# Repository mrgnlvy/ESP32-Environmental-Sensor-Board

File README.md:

# ESP32-Environmental-Sensor-Board

4-layer ESP32-C3 IoT PCB with USB-C charging and data transfer, along with environmental sensors, a battery charge manger,  an OLED display, and SD storage for remote data logging capabilities.

### Features

- **Microcontroller**: ESP32-C3-02 for Wi-Fi/BLE
- **Power Inputs**:
  - USB-C connector for charging and data transfer.
  - LiPo battery connector with onboard charging circuitry.
- **Sensors and Modules**:
  - BME280 for temperature, humidity, and pressure sensing.
  - Ambient light and sound sensors.
  - Mini SD card reader for data storage.
  - Flash memory for additional storage.
- **Power Management**: TP4056 IC for single-cell Li-ion battery charging with thermal regulation.
- **Battery Protection**: Integrated under-voltage lockout and trickle charging.
- **Display**: I2C OLED for real-time data visualization.
- **Indicators**: LED indicators for charge status (charging and full).

### Design

4-layer design:
- **Top**: Signals
- **Inner 1**: Ground Plane
- **Inner 2**: Power Plane
- **Bottom**: Signals

### Applications

- IoT edge devices for environmental monitoring.
- Battery-powered data logging systems.
- Prototyping platform for ESP32-based projects.

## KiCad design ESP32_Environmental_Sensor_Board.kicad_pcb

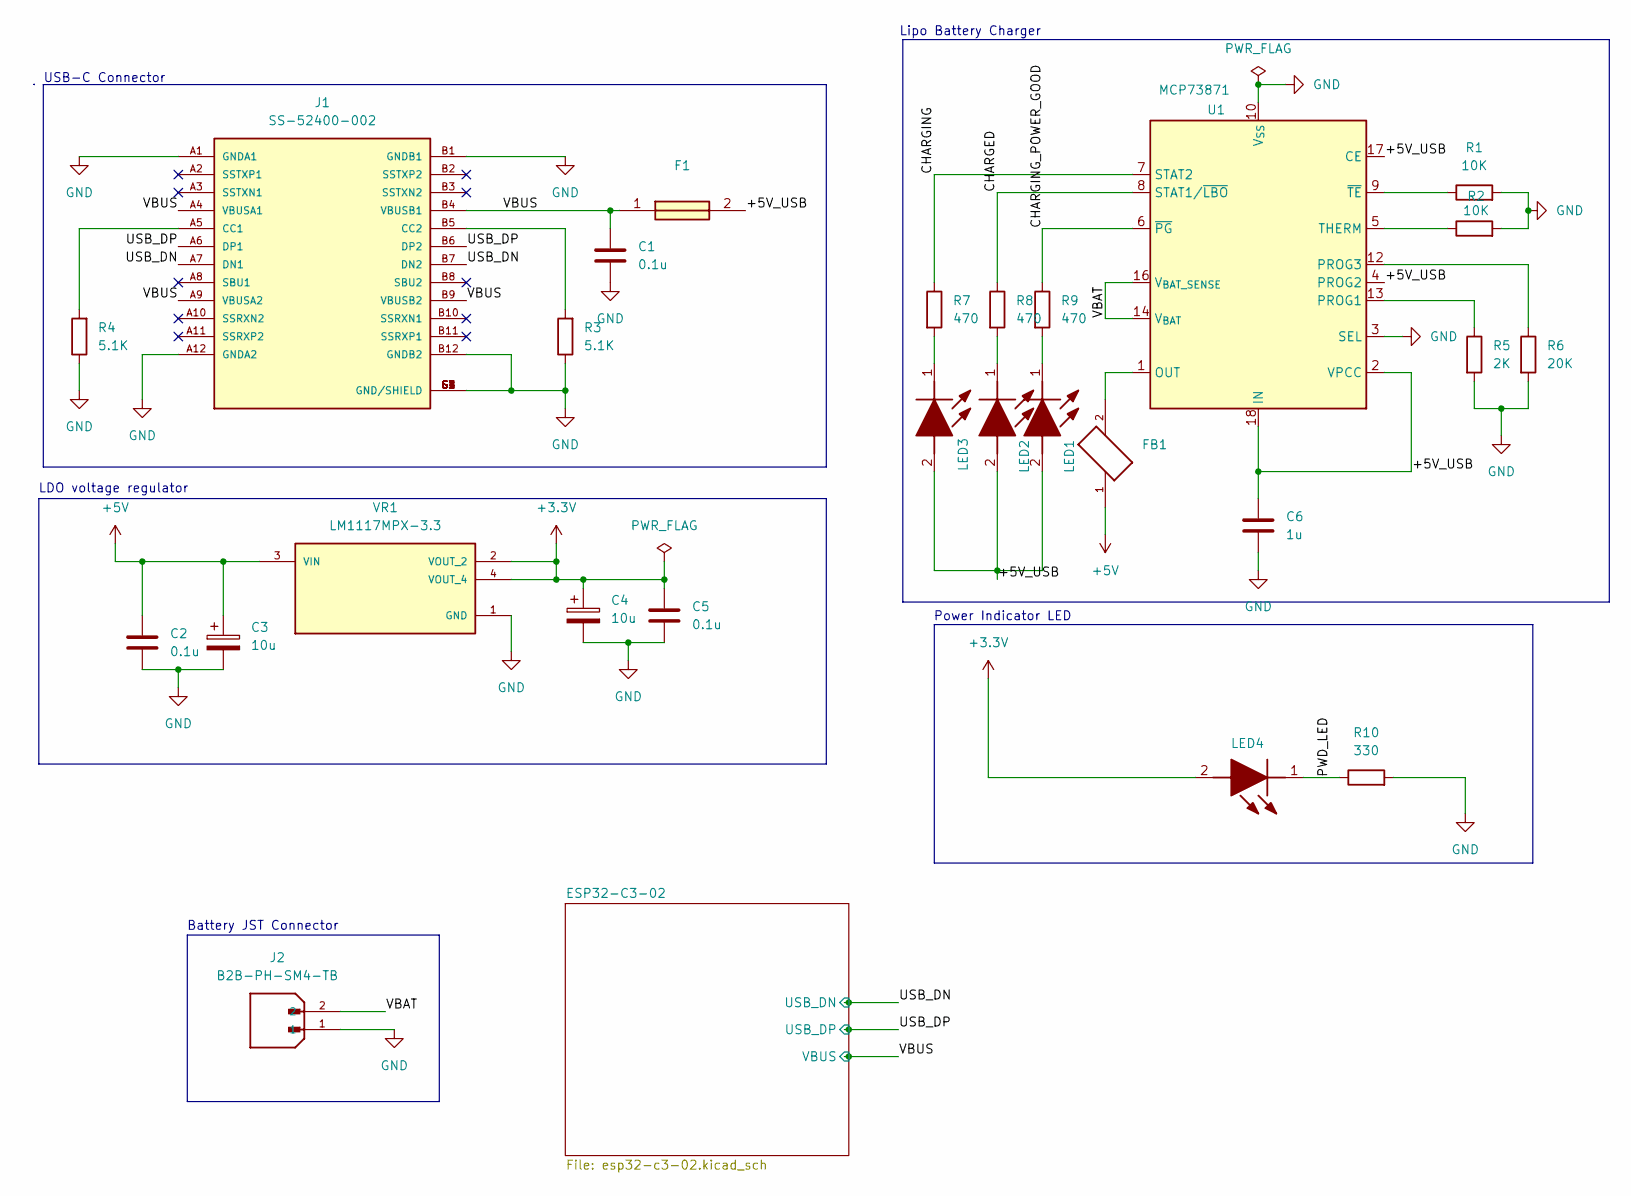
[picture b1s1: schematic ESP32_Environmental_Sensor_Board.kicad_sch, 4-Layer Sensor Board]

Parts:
C1, C2, C5: 0.1u; C_0805_2012Metric
C3, C4: 10u; T491A
C6: 1u; C_0805_2012Metric
F1: 0ZCH0110AF2E; FUSC3226X100N; Manufacturer_Part_Number 0ZCH0110AF2E
FB1: FBMJ2125HM330-T; BEADC2012X105N
J1: SS-52400-002; BELFUSE_SS-52400-002; PARTREV A0
J2: B2B-PH-SM4-TB; JST_B2B-PH-SM4-TB; PARTREV N/A
LED1: LTST-C170TBKT; LEDC2012X120N; Manufacturer_Part_Number LTST-C170TBKT; Mouser Part Number 859-LTST-C170TBKT
LED2: LTST-C170GKT; LEDC2012X120N; Manufacturer_Part_Number LTST-C170GKT; Mouser Part Number 859-LTST-C170GKT
LED3, LED4: LTST-C170KRKT; LEDC2012X120N; Manufacturer_Part_Number LTST-C170KRKT; Mouser Part Number 859-LTST-C170KRKT
R1, R2: 10K; R_0805_2012Metric
R3, R4: 5.1K; R_0805_2012Metric
R5: 2K; R_0805_2012Metric
R6: 20K; R_0805_2012Metric
R7, R8, R9: 470; R_0805_2012Metric
R10: 330; R_0805_2012Metric
U1: MCP73871; QFN-20-1EP_4x4mm_P0.5mm_EP2.5x2.5mm
VR1: LM1117MPX-3.3; VREG_LM1117MPX-3.3

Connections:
+3.3V: C4.1, C5.1, LED4.2 (A), VR1.2 (VOUT_2), VR1.4 (VOUT_4); also elsewhere on the board
+5V: C2.1, C3.1, FB1.1, VR1.3 (VIN)
/+5V_USB: C6.1, F1.2, LED1.2 (A), LED2.2 (A), LED3.2 (A), U1.2 (VPCC), U1.4 (PROG2), U1.17 (CE), U1.18 (IN), U1.19 (IN)
/CHARGED: R8.1, U1.8 (STAT1/~LBO)
/CHARGING: R7.1, U1.7 (STAT2)
/CHARGING_POWER_GOOD: R9.1, U1.6 (~PG)
/PWD_LED: LED4.1 (K), R10.1
/USB_DN: J1.A7 (DN1), J1.B7 (DN2); also elsewhere on the board
/USB_DP: J1.A6 (DP1), J1.B6 (DP2); also elsewhere on the board
/VBAT: J2.2, U1.14 (V_{BAT}), U1.15 (V_{BAT}), U1.16 (V_{BAT_SENSE})
/VBUS: C1.1, F1.1, J1.A4 (VBUSA1), J1.A9 (VBUSA2), J1.B4 (VBUSB1), J1.B9 (VBUSB2); also elsewhere on the board
GND: C1.2, C2.2, C3.2, C4.2, C5.2, C6.2, J1.A1 (GNDA1), J1.A12 (GNDA2), J1.B1 (GNDB1), J1.B12 (GNDB2), J1.G1 (GND/SHIELD), J1.G2 (GND/SHIELD), J1.G3 (GND/SHIELD), J1.G4 (GND/SHIELD), J1.S1 (GND/SHIELD), J1.S2 (GND/SHIELD), J1.S3 (GND/SHIELD), J1.S4 (GND/SHIELD), J2.1, R1.2, R2.2, R3.1, R4.1, R5.2, R6.2, R10.2, U1.3 (SEL), U1.10 (V_{SS}), U1.11 (V_{SS}), U1.21 (V_{SS}), VR1.1 (GND); also elsewhere on the board
unnamed: FB1.2, U1.1 (OUT), U1.20 (OUT)
unnamed: J1.A5 (CC1), R4.2
unnamed: J1.B5 (CC2), R3.2
unnamed: LED1.1 (K), R9.2
unnamed: LED2.1 (K), R8.2
unnamed: LED3.1 (K), R7.2
unnamed: R5.1, U1.13 (PROG1)
unnamed: R6.1, U1.12 (PROG3)
unnamed: R2.1, U1.5 (THERM)
unnamed: R1.1, U1.9 (~TE)

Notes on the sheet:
Battery JST Connector
USB-C Connector
Lipo Battery Charger
Power Indicator LED
LDO voltage regulator

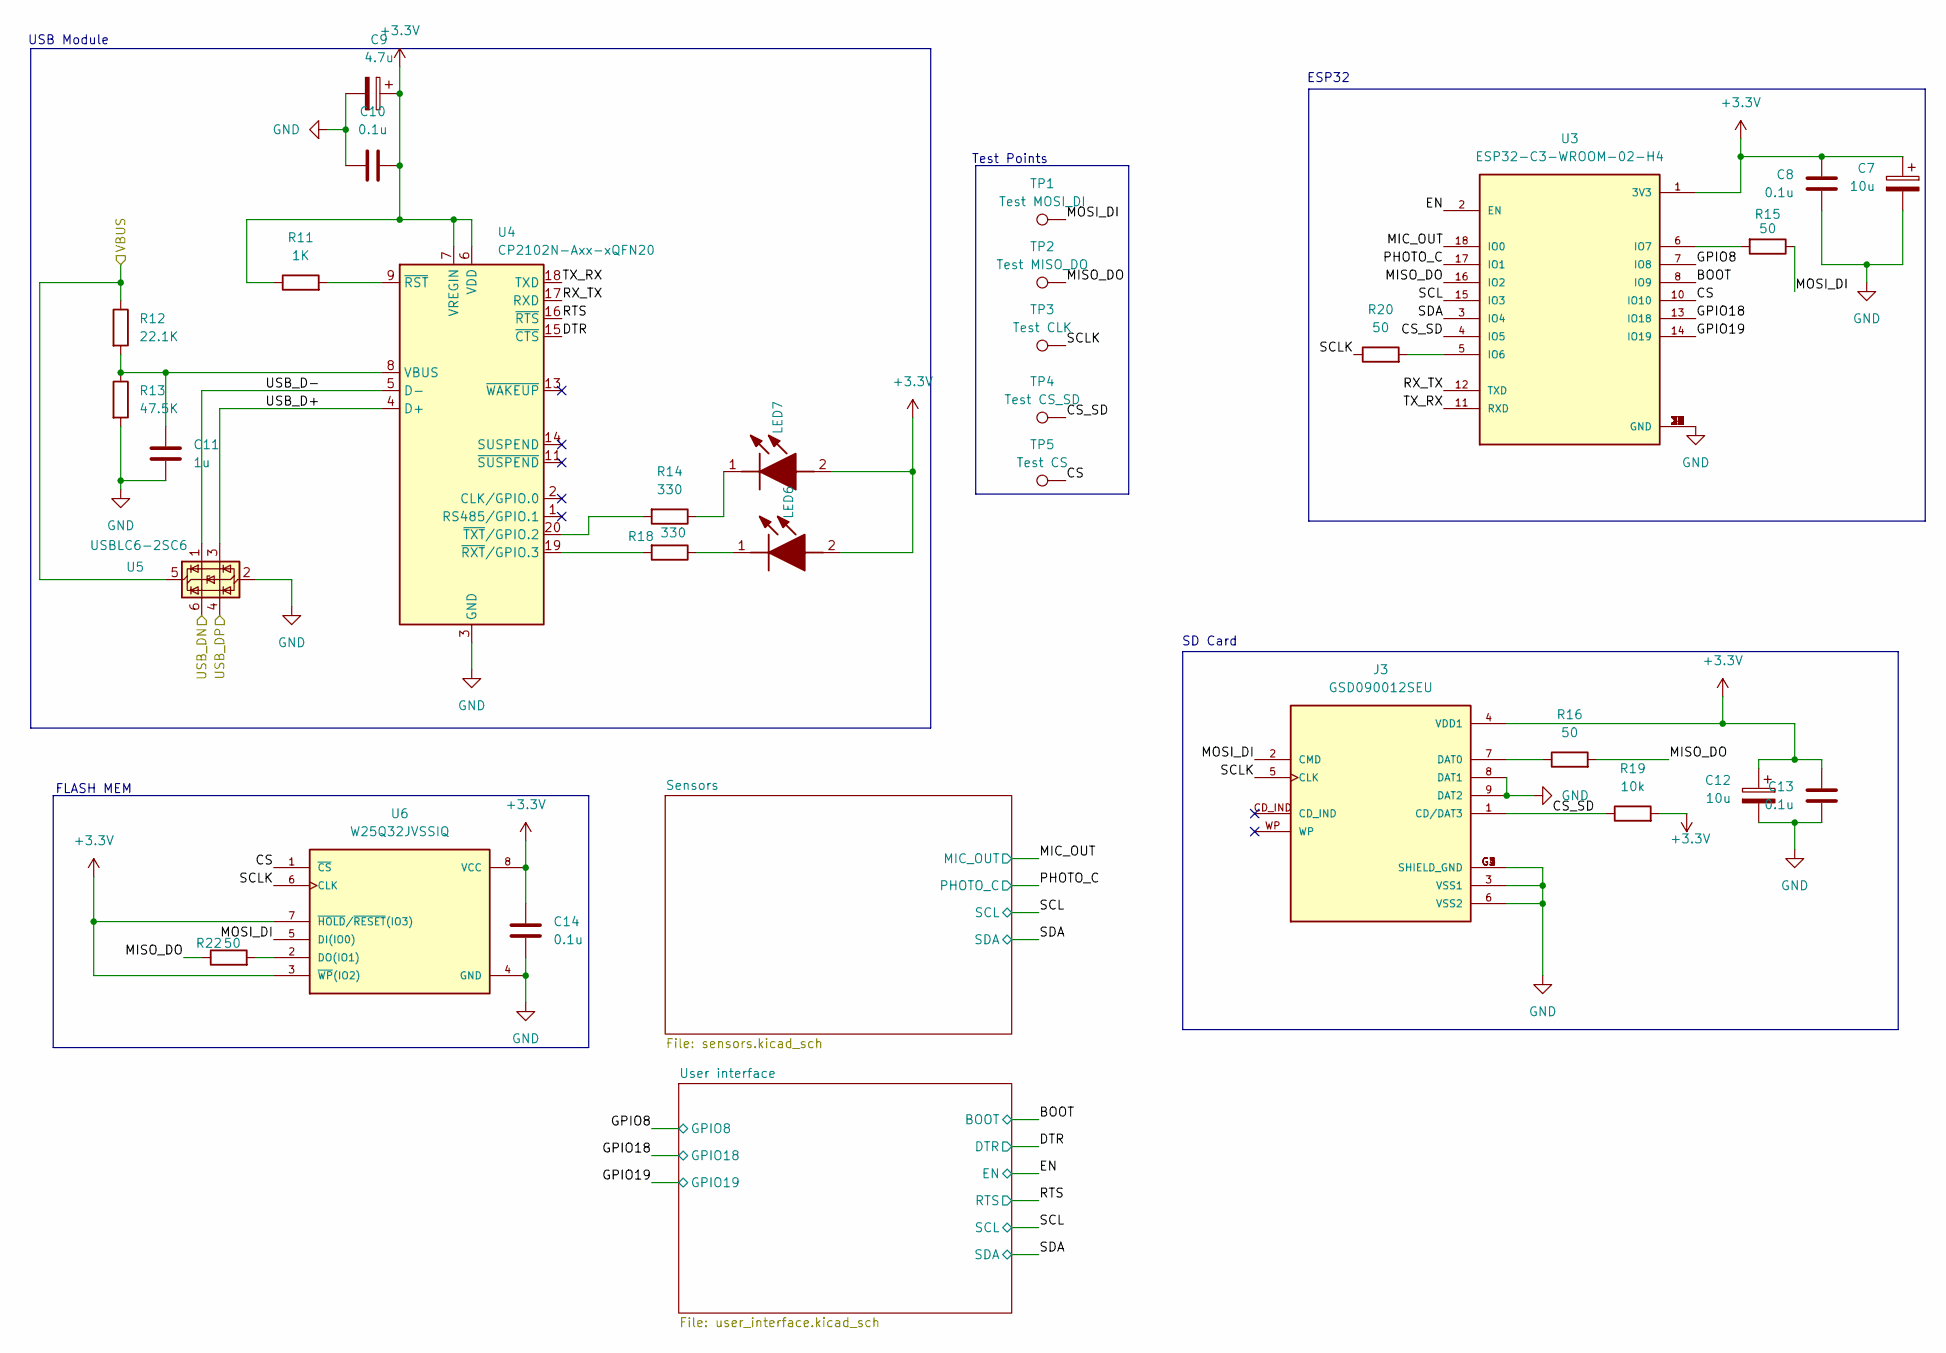
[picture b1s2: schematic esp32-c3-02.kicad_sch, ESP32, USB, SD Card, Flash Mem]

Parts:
C7, C12: 10u; T491A
C8, C10, C13, C14: 0.1u; C_0805_2012Metric
C9: 4.7u; T491A
C11: 1u; C_0805_2012Metric
J3: GSD090012SEU; AMPHENOL_GSD090012SEU; PARTREV E
LED6: LTST-C170TBKT; LEDC2012X120N; Manufacturer_Part_Number LTST-C170TBKT; Mouser Part Number 859-LTST-C170TBKT
LED7: LTST-C170GKT; LEDC2012X120N; Manufacturer_Part_Number LTST-C170GKT; Mouser Part Number 859-LTST-C170GKT
R11: 1K; R_0805_2012Metric
R12: 22.1K; R_0805_2012Metric
R13: 47.5K; R_0805_2012Metric
R14, R18: 330; R_0805_2012Metric
R15, R16, R20, R22: 50; R_0805_2012Metric
R19: 10k; R_0805_2012Metric
TP1: Test MOSI_DI; TestPoint_Pad_D1.0mm
TP2: Test MISO_DO; TestPoint_Pad_D1.0mm
TP3: Test CLK; TestPoint_Pad_D1.0mm
TP4: Test CS_SD; TestPoint_Pad_D1.0mm
TP5: Test CS; TestPoint_Pad_D1.0mm
U3: ESP32-C3-WROOM-02-H4; MODULE_ESP32-C3-WROOM-02-H4
U4: CP2102N-Axx-xQFN20; SiliconLabs_QFN-20-1EP_3x3mm_P0.5mm_EP1.8x1.8mm
U5: USBLC6-2SC6; SOT-23-6
U6: W25Q32JVSSIQ; SOIC127P790X216-8N; M_PART_NUMBER W25QXX

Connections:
+3.3V: C7.1, C8.1, C9.1, C10.2, C12.1, C13.1, C14.1, J3.4 (VDD1), LED6.2 (A), LED7.2 (A), R11.1, R19.2, U3.1 (3V3), U4.6 (VDD), U4.7 (VREGIN), U6.3 (~WP(IO2)), U6.7 (~HOLD/~RESET(IO3)), U6.8 (VCC); also elsewhere on the board
/ESP32-C3-02/BOOT: U3.8 (IO9); also elsewhere on the board
/ESP32-C3-02/CS: TP5.1, U3.10 (IO10), U6.1 (~CS)
/ESP32-C3-02/CS_SD: J3.1 (CD/DAT3), R19.1, TP4.1, U3.4 (IO5)
/ESP32-C3-02/DTR: U4.15 (~CTS); also elsewhere on the board
/ESP32-C3-02/EN: U3.2 (EN); also elsewhere on the board
/ESP32-C3-02/GPIO8: U3.7 (IO8); also elsewhere on the board
/ESP32-C3-02/GPIO18: U3.13 (IO18); also elsewhere on the board
/ESP32-C3-02/GPIO19: U3.14 (IO19); also elsewhere on the board
/ESP32-C3-02/MIC_OUT: U3.18 (IO0); also elsewhere on the board
/ESP32-C3-02/MISO_DO: R16.2, R22.1, TP2.1, U3.16 (IO2)
/ESP32-C3-02/MOSI_DI: J3.2 (CMD), R15.1, TP1.1, U6.5 (DI(IO0))
/ESP32-C3-02/PHOTO_C: U3.17 (IO1); also elsewhere on the board
/ESP32-C3-02/RTS: U4.16 (~RTS); also elsewhere on the board
/ESP32-C3-02/RX_TX: U3.12 (TXD), U4.17 (RXD)
/ESP32-C3-02/SCL: U3.15 (IO3); also elsewhere on the board
/ESP32-C3-02/SCLK: J3.5 (CLK), R20.1, TP3.1, U6.6 (CLK)
/ESP32-C3-02/SDA: U3.3 (IO4); also elsewhere on the board
/ESP32-C3-02/TX_RX: U3.11 (RXD), U4.18 (TXD)
/ESP32-C3-02/USB_D+: U4.4 (D+), U5.3 (I/O2)
/ESP32-C3-02/USB_D-: U4.5 (D-), U5.1 (I/O1)
/USB_DN: U5.6 (I/O1); also elsewhere on the board
/USB_DP: U5.4 (I/O2); also elsewhere on the board
/VBUS: R12.1, U5.5 (VBUS); also elsewhere on the board
GND: C7.2, C8.2, C9.2, C10.1, C11.2, C12.2, C13.2, C14.2, J3.3 (VSS1), J3.6 (VSS2), J3.8 (DAT1), J3.9 (DAT2), J3.G1 (SHIELD_GND), J3.G2 (SHIELD_GND), J3.G3 (SHIELD_GND), J3.G4 (SHIELD_GND), R13.2, U3.9 (GND), U3.19 (GND), U3.20 (GND), U3.21 (GND), U3.22 (GND), U3.23 (GND), U3.24 (GND), U3.25 (GND), U3.26 (GND), U3.27 (GND), U3.28 (GND), U3.29 (GND), U3.30 (GND), U3.31 (GND), U3.32 (GND), U3.33 (GND), U3.34 (GND), U3.35 (GND), U3.36 (GND), U3.37 (GND), U3.38 (GND), U3.39 (GND), U4.3 (GND), U4.12 (GND), U4.21 (GND), U5.2 (GND), U6.4 (GND); also elsewhere on the board
unnamed: J3.7 (DAT0), R16.1
unnamed: LED6.1 (K), R18.1
unnamed: LED7.1 (K), R14.1
unnamed: R20.2, U3.5 (IO6)
unnamed: R15.2, U3.6 (IO7)
unnamed: C11.1, R12.2, R13.1, U4.8 (VBUS)
unnamed: R11.2, U4.9 (~RST)
unnamed: R18.2, U4.19 (~RXT/GPIO.3)
unnamed: R14.2, U4.20 (~TXT/GPIO.2)
unnamed: R22.2, U6.2 (DO(IO1))

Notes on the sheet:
SD Card
USB Module
FLASH MEM
Test Points
ESP32

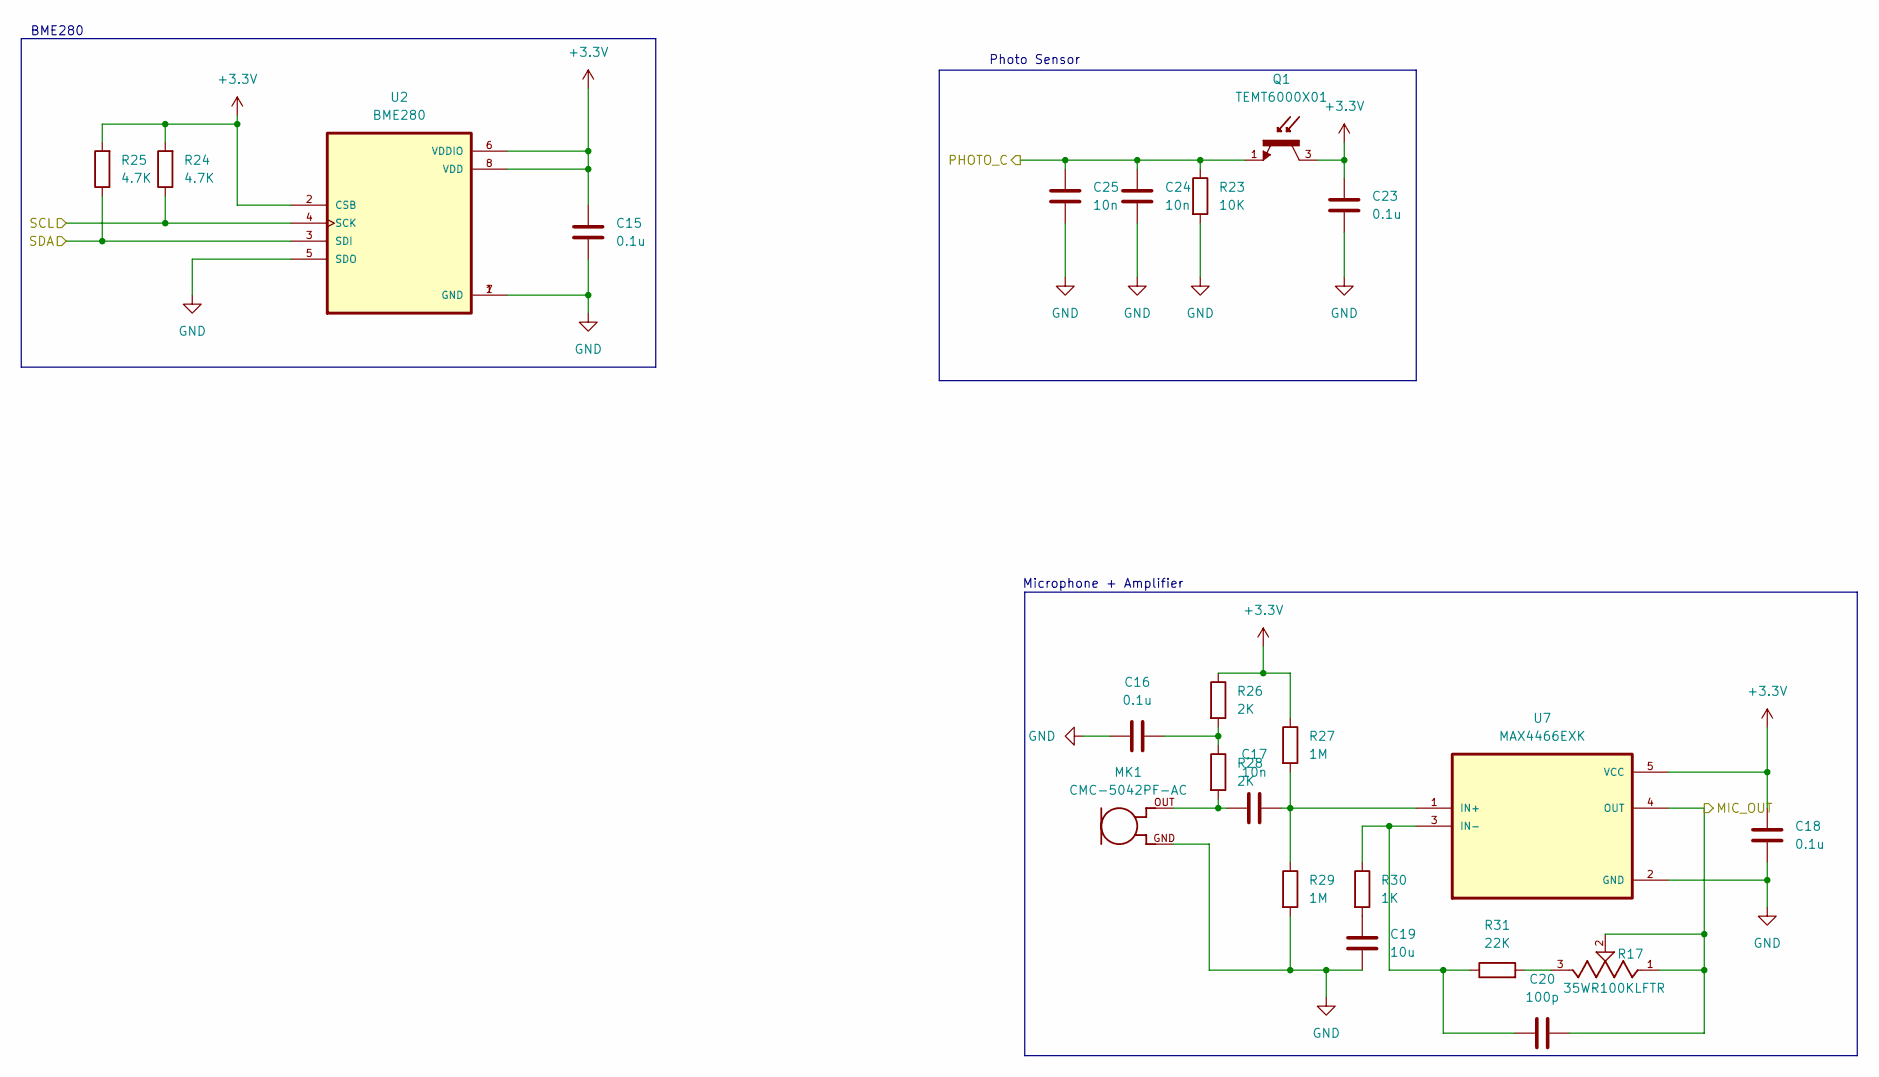
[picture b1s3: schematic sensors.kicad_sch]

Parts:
C15, C16, C18, C23: 0.1u; C_0805_2012Metric
C17: 10n; R_0805_2012Metric
C19: 10u; C_0805_2012Metric
C20: 100p; C_0805_2012Metric
C24, C25: 10n; C_0805_2012Metric
MK1: CMC-5042PF-AC; CUI_CMC-5042PF-AC
Q1: TEMT6000X01; TRANS_TEMT6000X01; PARTREV 1.9
R17: 35WR100KLFTR; TRIM_35WR100KLFTR; PARTREV D
R23: 10K; R_0805_2012Metric
R24, R25: 4.7K; R_0805_2012Metric
R26, R28: 2K; R_0805_2012Metric
R27, R29: 1M; R_0805_2012Metric
R30: 1K; R_0805_2012Metric
R31: 22K; R_0805_2012Metric
U2: BME280; PSON65P250X250X100-8N
U7: MAX4466EXK; SOT65P210X110-5N

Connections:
+3.3V: C15.1, C18.1, C23.1, Q1.3, R24.2, R25.2, R26.1, R27.1, U2.2 (CSB), U2.6 (VDDIO), U2.8 (VDD), U7.5 (VCC); also elsewhere on the board
/ESP32-C3-02/MIC_OUT: C20.2, R17.1, R17.2, U7.4 (OUT); also elsewhere on the board
/ESP32-C3-02/PHOTO_C: C24.1, C25.1, Q1.1, R23.1; also elsewhere on the board
/ESP32-C3-02/SCL: R24.1, U2.4 (SCK); also elsewhere on the board
/ESP32-C3-02/SDA: R25.1, U2.3 (SDI); also elsewhere on the board
GND: C15.2, C16.1, C18.2, C19.2, C23.2, C24.2, C25.2, MK1.GND, R23.2, R29.2, U2.1 (GND), U2.5 (SDO), U2.7 (GND), U7.2 (GND); also elsewhere on the board
unnamed: C16.2, R26.2, R28.1
unnamed: C17.1, MK1.OUT, R28.2
unnamed: C19.1, R30.2
unnamed: R17.3, R31.2
unnamed: C17.2, R27.2, R29.1, U7.1 (IN+)
unnamed: C20.1, R30.1, R31.1, U7.3 (IN-)

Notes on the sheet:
BME280
Photo Sensor
Microphone + Amplifier

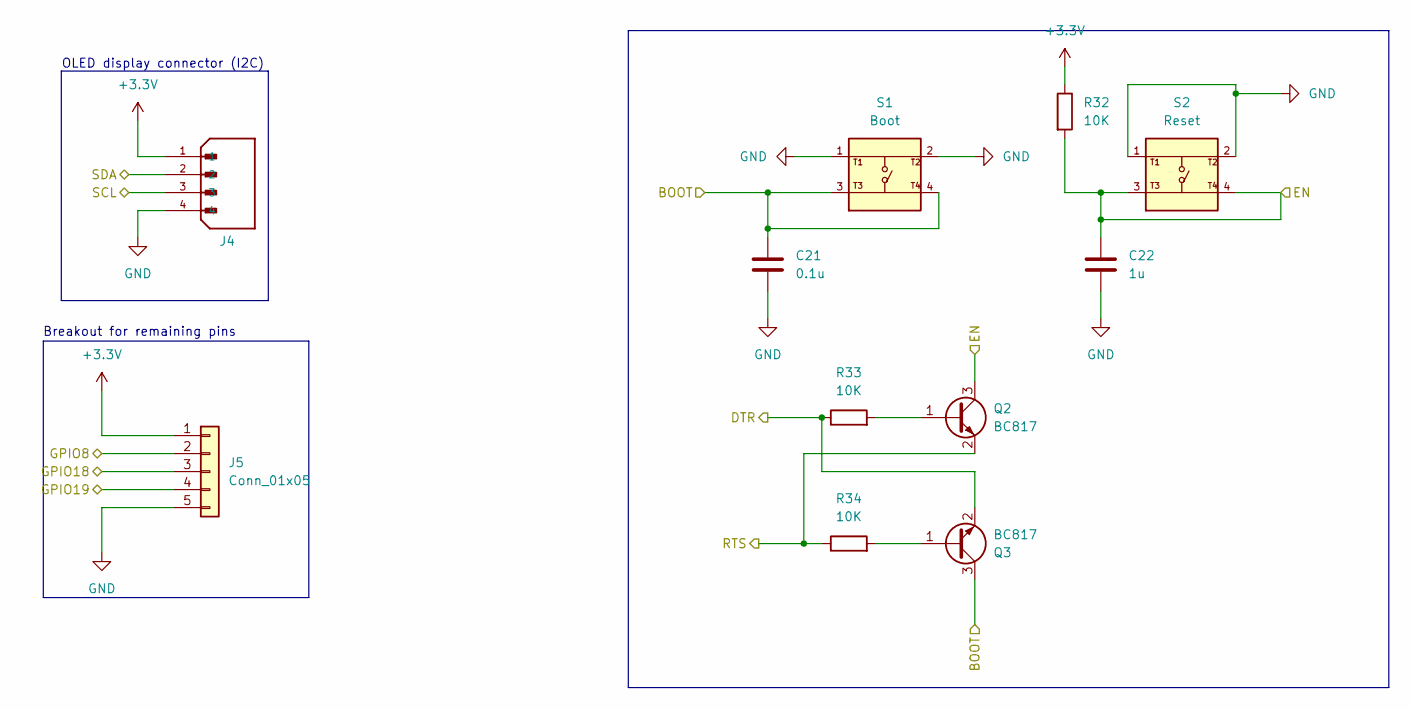
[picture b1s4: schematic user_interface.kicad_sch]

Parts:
C21: 0.1u; C_0805_2012Metric
C22: 1u; C_0805_2012Metric
J4: B4B-XH-AM__LF__SN_; JST_B4B-XH-AM__LF__SN_; PARTREV N/A
J5: Conn_01x05; PinHeader_1x05_P2.54mm_Vertical
Q2, Q3: BC817; SOT-23
R32, R33, R34: 10K; R_0805_2012Metric
S1: Boot; SW_USLPT2819DT2TR; PARTREV P
S2: Reset; SW_USLPT2819DT2TR; PARTREV P

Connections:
+3.3V: J4.1, J5.1, R32.1; also elsewhere on the board
/ESP32-C3-02/BOOT: C21.1, Q3.3 (C), S1.3, S1.4; also elsewhere on the board
/ESP32-C3-02/DTR: Q3.2 (E), R33.1; also elsewhere on the board
/ESP32-C3-02/EN: C22.1, Q2.3 (C), R32.2, S2.3, S2.4; also elsewhere on the board
/ESP32-C3-02/GPIO8: J5.2; also elsewhere on the board
/ESP32-C3-02/GPIO18: J5.3; also elsewhere on the board
/ESP32-C3-02/GPIO19: J5.4; also elsewhere on the board
/ESP32-C3-02/RTS: Q2.2 (E), R34.1; also elsewhere on the board
/ESP32-C3-02/SCL: J4.3; also elsewhere on the board
/ESP32-C3-02/SDA: J4.2; also elsewhere on the board
GND: C21.2, C22.2, J4.4, J5.5, S1.1, S1.2, S2.1, S2.2; also elsewhere on the board
unnamed: Q2.1 (B), R33.2
unnamed: Q3.1 (B), R34.2

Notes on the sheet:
OLED display connector (I2C)
Breakout for remaining pins

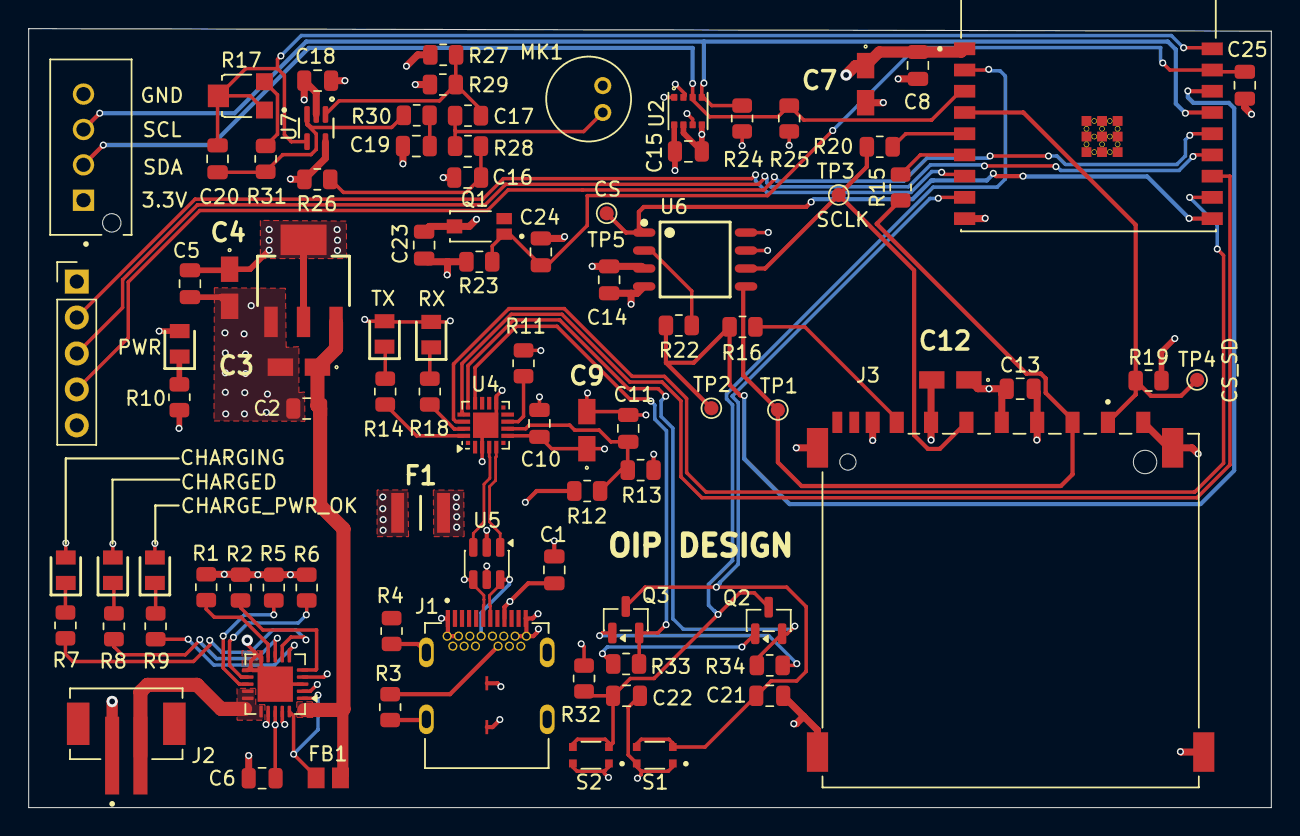
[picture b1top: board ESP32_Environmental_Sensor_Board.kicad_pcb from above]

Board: 4 copper layers, 87.8 x 55.0 mm, 90 parts (0 on the bottom side), 60 nets.

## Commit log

2026-03-26 Intitial commit
2026-03-26 add README
